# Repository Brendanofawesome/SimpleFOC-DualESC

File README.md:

# SimpleFOC Dual ESC

This repository contains the hardware design files for a compact dual-motor BLDC controller built around the SimpleFOC ecosystem.  

The board is designed to run two 3-phase motors independently with field-oriented control (FOC) using an STM32G4 microcontroller.  

It is also designed to fit under JLCPCB's $2 PCB deal with economic assembly

## What the device does

The controller takes a single high-voltage DC input and drives two BLDC motors through two independent 3-phase power stages.  
Each motor stage uses a dedicated gate driver and current-sense path so firmware can regulate torque/current, speed, and position.

At a high level, the board:

- Uses up to 36 V to power 3-phase outputs for **Motor 1** and **Motor 2**
- Uses dual DRV8323-based driver stages for 6-PWM control of each motor
- Measures phase/motor current for closed-loop control and protection
- Interfaces with Hall sensors for rotor position feedback
- Exposes control/debug interfaces including I2C, SPI headers, USB-C, reset, and programming pins

## Hardware highlights

- **MCU:** STM32G474CBTx (FOC-capable Cortex-M4)
- **Power input:** XT60 connector
- **Motor outputs:** Two MR60 3-phase motor connectors
- **Board outline:** 50 mm × 50 mm (from KiCad PCB edge cuts)
- **Power stage:** Dual 3-phase inverter architecture (6 MOSFETs per motor stage)

## Repository layout

- `specifications.md`  
  Project specification draft (electrical, control, thermal, and interface targets).
- `KiCad/simpleFOC Dual Motor Controller.kicad_pro`  
  Top-level KiCad project.
- `KiCad/simpleFOC Dual Motor Controller.kicad_sch`  
  Top-level schematic with MCU, power, interfaces, and two motor-driver hierarchical sheets.
- `KiCad/DriverStage.kicad_sch`  
  Per-motor driver stage (reused for Motor Driver 1 and Motor Driver 2).
- `KiCad/simpleFOC Dual Motor Controller.kicad_pcb`  
  PCB layout and silkscreen connector labels.

## Current status

This repo currently provides hardware design and specification files.  
Firmware implementation and full bring-up documentation are not yet included here.

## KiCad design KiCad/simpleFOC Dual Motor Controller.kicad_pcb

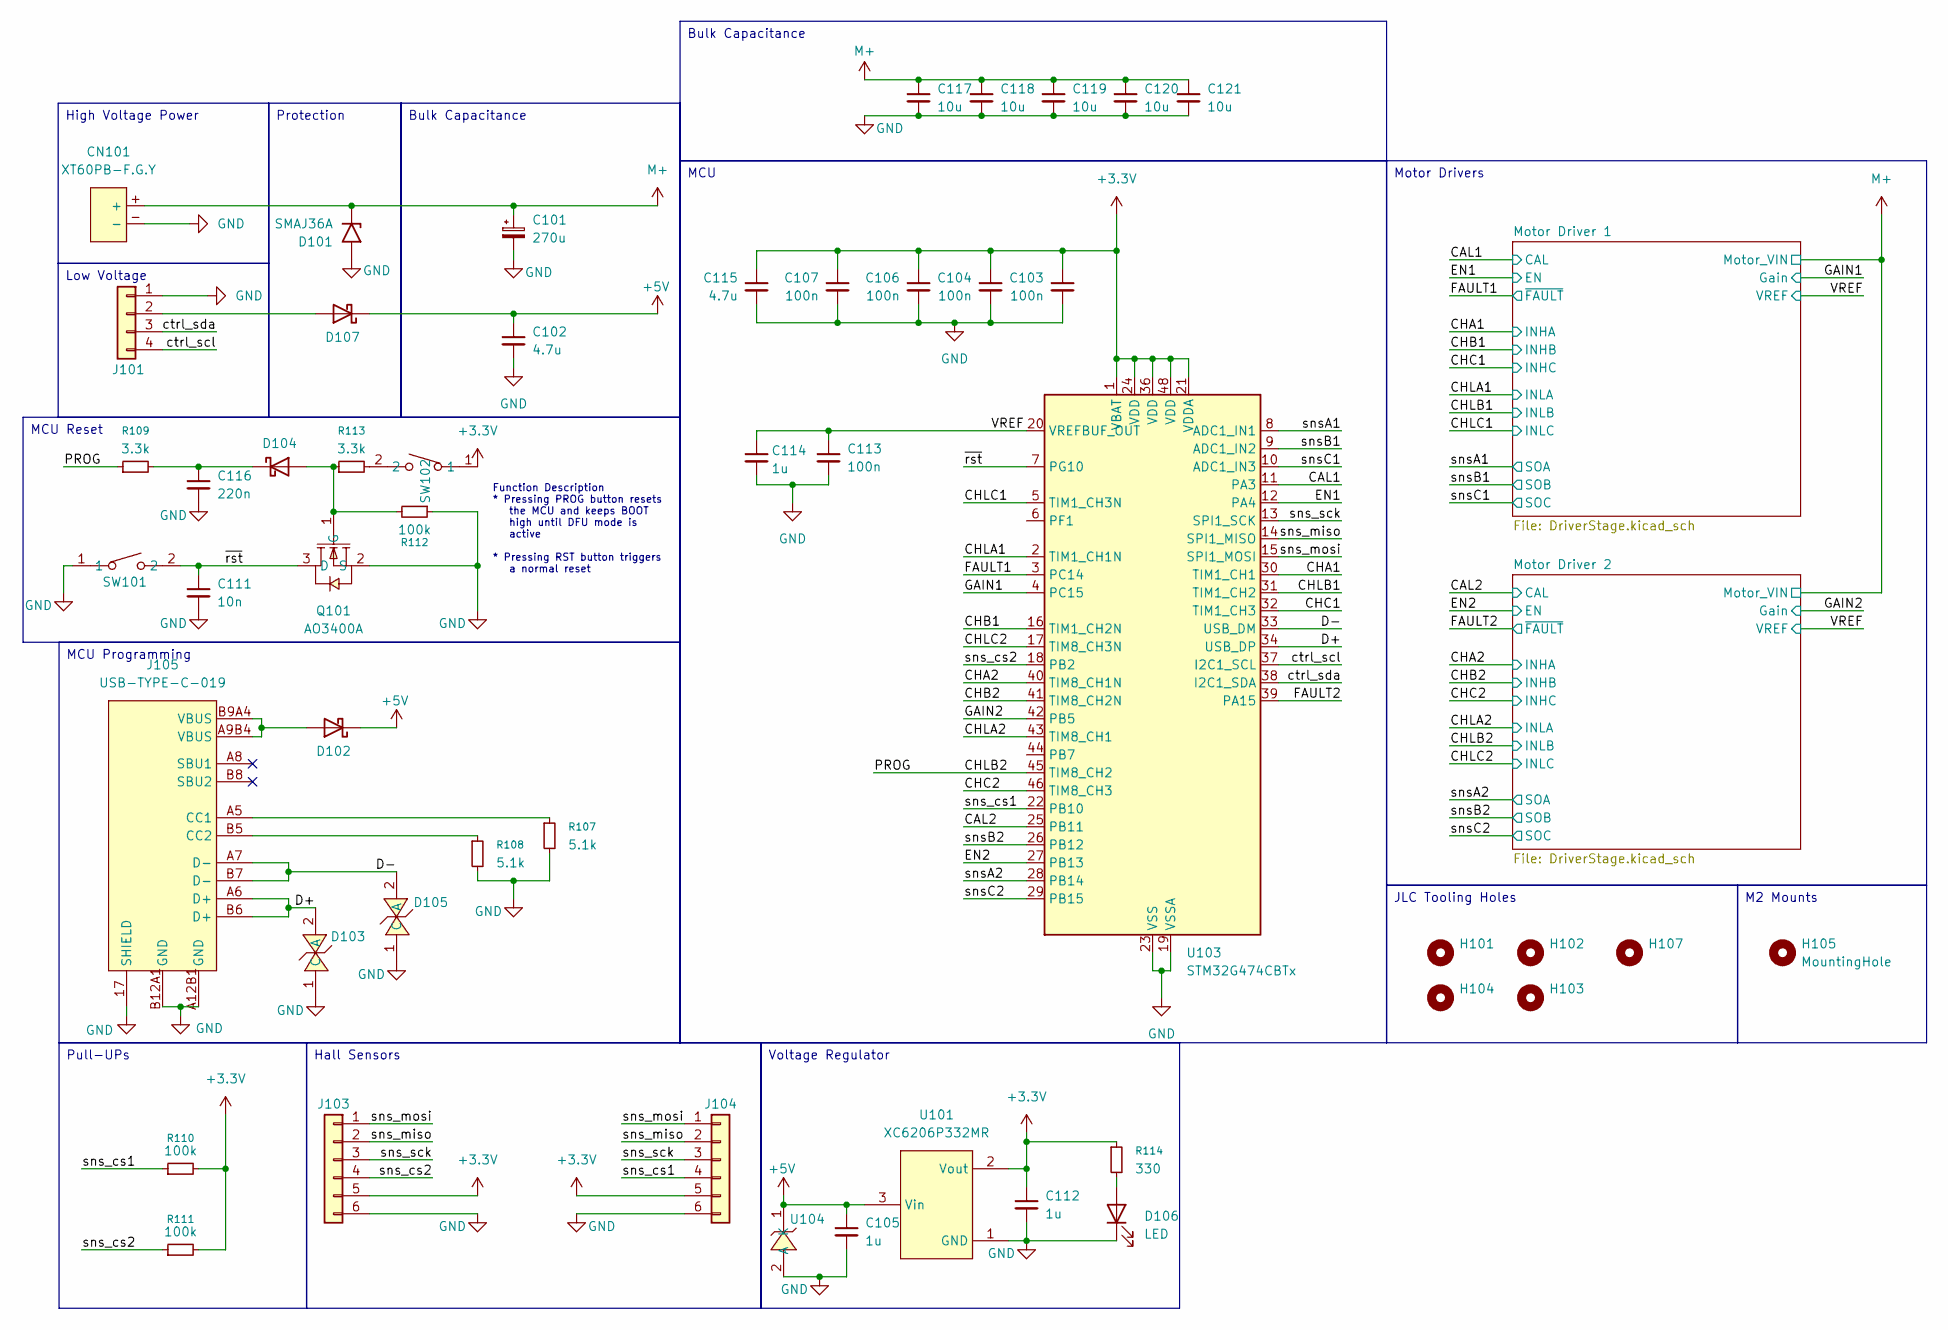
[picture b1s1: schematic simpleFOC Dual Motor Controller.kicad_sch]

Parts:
C101: 270u; CAP-TH_BD8.0-P3.50-D0.6-FD; LCSC C55079818
C102, C115: 4.7u; C_0402_1005Metric; LCSC C23733
C103, C104, C106, C107, C113: 100n; C_0402_1005Metric; LCSC C307331
C105, C112, C114: 1u; C_0402_1005Metric; LCSC C52923
C111: 10n; C_0402_1005Metric; LCSC C15195
C116: 220n; C_0402_1005Metric; LCSC C16772
C117, C118, C119, C120, C121: 10u; C_1206_3216Metric; LCSC C13585
CN101: XT60PB-F.G.Y; CONN-TH_XT60PB-F.G.Y; MPN XT60PB-F.G.Y; LCSC Part C19268038
D101: SMAJ36A; D_SMA; LCSC C19077550
D102, D104, D107: 1N5819WS; D_SOD-323; LCSC C191023
D103, D105: H5VL10B; SOD-882_L1.0-W0.6-BI; MPN H5VL10B; LCSC Part C7420372
D106: LED; LED_0603_1608Metric; LCSC C2290
H101, H102, H103, H104, H107: MountingHole; JLC_Tooling_Hole
H105: MountingHole; MountingHole_2.2mm_M2
J101: Conn_01x04; JST_PH_B4B-PH-K_1x04_P2.00mm_Vertical; LCSC C131334
J103, J104: Conn_01x06; JST_PH_B6B-PH-K_1x06_P2.00mm_Vertical; LCSC C131342
J105: USB-TYPE-C-019; TYPE-C-SMD_HX-TYPE-C-16PIN; MPN USB-TYPE-C-019; LCSC Part C2927039
Q101: AO3400A; SOT-23-3_L2.9-W1.3-P1.90-LS2.4-BR; MPN AO3400A; LCSC Part C20917
R107, R108: 5.1k; R_0402_1005Metric; LCSC C25905
R109, R113: 3.3k; R_0402_1005Metric; LCSC C25890
R110, R111, R112: 100k; R_0402_1005Metric; LCSC C25741
R114: 330; R_0402_1005Metric; LCSC C25104
SW101, SW102: TS-1088-AR02016; SW-SMD_L3.9-W3.0-P4.45; MPN TS-1088-AR02016; LCSC Part C720477
U101: XC6206P332MR; SOT-23-3_L2.9-W1.6-P1.90-LS2.8-BR; MPN XC6206P332MR-G; LCSC Part C5446
U103: STM32G474CBTx; LQFP-48_7x7mm_P0.5mm; LCSC C730123
U104: H5VND5UB; SOD-523F_L1.7-W0.9-LS1.7-RD; MPN H5VND5UB; LCSC Part C20615819

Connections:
+3.3V: C103.1, C104.1, C106.1, C107.1, C112.1, C115.1, J103.5, J104.5, R110.2, R111.2, R114.1, SW102.1, U101.2 (Vout), U103.1 (VBAT), U103.21 (VDDA), U103.24 (VDD), U103.36 (VDD), U103.48 (VDD); also elsewhere on the board
+5V: C102.1, C105.1, D102.1 (K), D107.1 (K), U101.3 (Vin), U104.1 (K)
/CAL1: U103.11 (PA3); also elsewhere on the board
/CAL2: U103.25 (PB11); also elsewhere on the board
/CHA1: U103.30 (TIM1_CH1); also elsewhere on the board
/CHA2: U103.40 (TIM8_CH1N); also elsewhere on the board
/CHB1: U103.16 (TIM1_CH2N); also elsewhere on the board
/CHB2: U103.41 (TIM8_CH2N); also elsewhere on the board
/CHC1: U103.32 (TIM1_CH3); also elsewhere on the board
/CHC2: U103.46 (TIM8_CH3); also elsewhere on the board
/CHLA1: U103.2 (TIM1_CH1N); also elsewhere on the board
/CHLA2: U103.43 (TIM8_CH1); also elsewhere on the board
/CHLB1: U103.31 (TIM1_CH2); also elsewhere on the board
/CHLB2: R109.1, U103.45 (TIM8_CH2); also elsewhere on the board
/CHLC1: U103.5 (TIM1_CH3N); also elsewhere on the board
/CHLC2: U103.17 (TIM8_CH3N); also elsewhere on the board
/D+: D103.2 (A), J105.A6 (D+), J105.B6 (D+), U103.34 (USB_DP)
/D-: D105.2 (A), J105.A7 (D-), J105.B7 (D-), U103.33 (USB_DM)
/EN1: U103.12 (PA4); also elsewhere on the board
/EN2: U103.27 (PB13); also elsewhere on the board
/FAULT1: U103.3 (PC14); also elsewhere on the board
/FAULT2: U103.39 (PA15); also elsewhere on the board
/GAIN1: U103.4 (PC15); also elsewhere on the board
/GAIN2: U103.42 (PB5); also elsewhere on the board
/VREF: C113.1, C114.1, U103.20 (VREFBUF_OUT); also elsewhere on the board
/ctrl_scl: J101.4, U103.37 (I2C1_SCL)
/ctrl_sda: J101.3, U103.38 (I2C1_SDA)
/snsA1: U103.8 (ADC1_IN1); also elsewhere on the board
/snsA2: U103.28 (PB14); also elsewhere on the board
/snsB1: U103.9 (ADC1_IN2); also elsewhere on the board
/snsB2: U103.26 (PB12); also elsewhere on the board
/snsC1: U103.10 (ADC1_IN3); also elsewhere on the board
/snsC2: U103.29 (PB15); also elsewhere on the board
/sns_cs1: J104.4, R110.1, U103.22 (PB10)
/sns_cs2: J103.4, R111.1, U103.18 (PB2)
/sns_miso: J103.2, J104.2, U103.14 (SPI1_MISO)
/sns_mosi: J103.1, J104.1, U103.15 (SPI1_MOSI)
/sns_sck: J103.3, J104.3, U103.13 (SPI1_SCK)
/~rst: C111.1, Q101.3 (D), SW101.2, U103.7 (PG10)
GND: C101.2, C102.2, C103.2, C104.2, C105.2, C106.2, C107.2, C111.2, C112.2, C113.2, C114.2, C115.2, C116.2, C117.2, C118.2, C119.2, C120.2, C121.2, CN101.-, D101.2 (A2), D103.1 (C), D105.1 (C), D106.1 (K), J101.1, J103.6, J104.6, J105.17 (SHIELD), J105.A12B1 (GND), J105.B12A1 (GND), Q101.2 (S), R107.2, R108.2, R112.1, SW101.1, U101.1 (GND), U103.19 (VSSA), U103.23 (VSS), U103.35 (VSS), U103.47 (VSS), U104.2 (A); also elsewhere on the board
M+: C101.1, C117.1, C118.1, C119.1, C120.1, C121.1, CN101.+, D101.1 (A1); also elsewhere on the board
unnamed: D102.2 (A), J105.A9B4 (VBUS), J105.B9A4 (VBUS)
unnamed: D104.2 (A), Q101.1 (G), R112.2, R113.1
unnamed: C116.1, D104.1 (K), R109.2
unnamed: D106.2 (A), R114.2
unnamed: D107.2 (A), J101.2
unnamed: J105.A5 (CC1), R107.1
unnamed: J105.B5 (CC2), R108.1
unnamed: R113.2, SW102.2

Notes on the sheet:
Function Description * Pressing PROG button resets the MCU and keeps BOOT high until DFU mode is active * Pressing RST button triggers a normal reset
MCU
MCU Reset
Bulk Capacitance
Pull-UPs
JLC Tooling Holes
High Voltage Power
Hall Sensors
Protection
Motor Drivers
Low Voltage
Voltage Regulator
M2 Mounts
MCU Programming

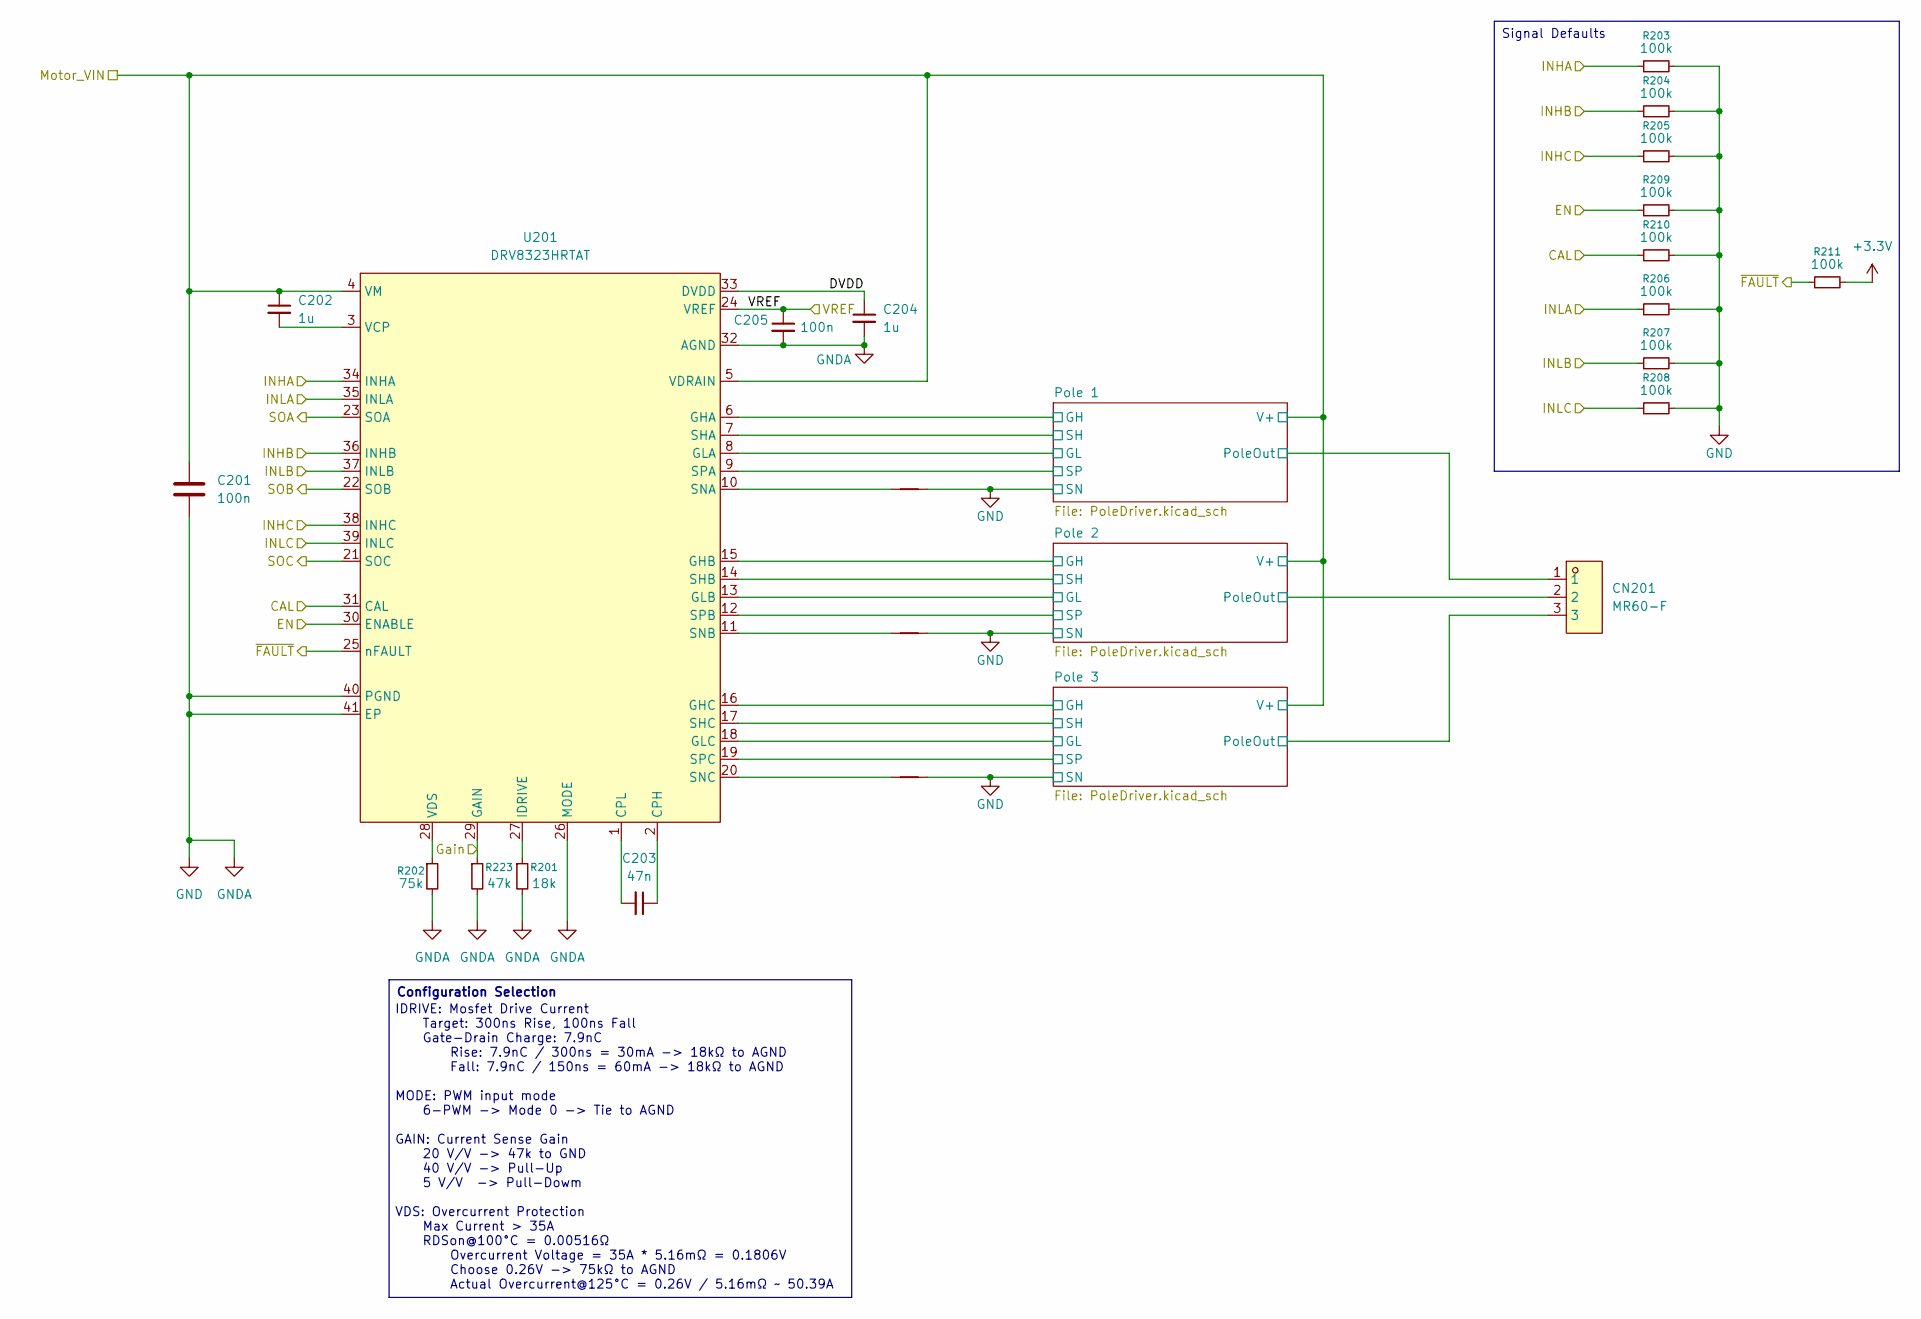
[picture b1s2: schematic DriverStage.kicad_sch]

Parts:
C201, C205: 100n; C_0402_1005Metric; LCSC C307331
C202: 1u; C_0603_1608Metric; LCSC C15849
C203: 47n; C_0603_1608Metric; LCSC C1622
C204: 1u; C_0402_1005Metric; LCSC C52923
CN201: MR60-F; CONN-TH_3P-P5.50_MR60-F; MPN MR60-F; LCSC Part C9900023305
NT201, NT202, NT203: NetTie_2; NetTie0.127mm
R201: 18k; R_0402_1005Metric; LCSC C25762
R202: 75k; R_0402_1005Metric; LCSC C25798
R203, R204, R205, R206, R207, R208, R209, R210, R211: 100k; R_0402_1005Metric; LCSC C25741
R223: 47k; R_0402_1005Metric; LCSC C25792
U201: DRV8323HRTAT; WQFN-40_L6.0-W6.0-P0.50-TL-EP4.2; MPN DRV8323HRTAT; LCSC Part C2150673

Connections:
+3.3V: R211.2; also elsewhere on the board
/CAL1: R210.1, U201.31 (CAL); also elsewhere on the board
/CHA1: R203.1, U201.34 (INHA); also elsewhere on the board
/CHB1: R204.1, U201.36 (INHB); also elsewhere on the board
/CHC1: R205.1, U201.38 (INHC); also elsewhere on the board
/CHLA1: R206.1, U201.35 (INLA); also elsewhere on the board
/CHLB1: R207.1, U201.37 (INLB); also elsewhere on the board
/CHLC1: R208.1, U201.39 (INLC); also elsewhere on the board
/EN1: R209.1, U201.30 (ENABLE); also elsewhere on the board
/FAULT1: R211.1, U201.25 (nFAULT); also elsewhere on the board
/GAIN1: R223.1, U201.29 (GAIN); also elsewhere on the board
/Motor Driver 1/DVDD: C204.1, U201.33 (DVDD)
/Motor Driver 1/Pole 1/GH: U201.6 (GHA); also elsewhere on the board
/Motor Driver 1/Pole 1/GL: U201.8 (GLA); also elsewhere on the board
/Motor Driver 1/Pole 1/PoleOut: CN201.1, U201.7 (SHA); also elsewhere on the board
/Motor Driver 1/Pole 1/SP: U201.9 (SPA); also elsewhere on the board
/Motor Driver 1/Pole 2/GH: U201.15 (GHB); also elsewhere on the board
/Motor Driver 1/Pole 2/GL: U201.13 (GLB); also elsewhere on the board
/Motor Driver 1/Pole 2/PoleOut: CN201.2, U201.14 (SHB); also elsewhere on the board
/Motor Driver 1/Pole 2/SP: U201.12 (SPB); also elsewhere on the board
/Motor Driver 1/Pole 3/GH: U201.16 (GHC); also elsewhere on the board
/Motor Driver 1/Pole 3/GL: U201.18 (GLC); also elsewhere on the board
/Motor Driver 1/Pole 3/PoleOut: CN201.3, U201.17 (SHC); also elsewhere on the board
/Motor Driver 1/Pole 3/SP: U201.19 (SPC); also elsewhere on the board
/VREF: C205.1, U201.24 (VREF); also elsewhere on the board
/snsA1: U201.23 (SOA); also elsewhere on the board
/snsB1: U201.22 (SOB); also elsewhere on the board
/snsC1: U201.21 (SOC); also elsewhere on the board
GND: C201.2, C204.2, C205.2, NT201.2, NT202.2, NT203.2, R201.2, R202.2, R203.2, R204.2, R205.2, R206.2, R207.2, R208.2, R209.2, R210.2, R223.2, U201.26 (MODE), U201.32 (AGND), U201.40 (PGND), U201.41 (EP); also elsewhere on the board
M+: C201.1, C202.1, U201.4 (VM), U201.5 (VDRAIN); also elsewhere on the board
unnamed: C203.1, U201.2 (CPH)
unnamed: C203.2, U201.1 (CPL)
unnamed: R201.1, U201.27 (IDRIVE)
unnamed: NT201.1, U201.10 (SNA)
unnamed: NT202.1, U201.11 (SNB)
unnamed: NT203.1, U201.20 (SNC)
unnamed: C202.2, U201.3 (VCP)
unnamed: R202.1, U201.28 (VDS)

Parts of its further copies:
C206, C209: 100n; C_0402_1005Metric; LCSC C307331
C207: 1u; C_0603_1608Metric; LCSC C15849
C208: 47n; C_0603_1608Metric; LCSC C1622
C210: 1u; C_0402_1005Metric; LCSC C52923
CN202: MR60-F; CONN-TH_3P-P5.50_MR60-F; MPN MR60-F; LCSC Part C9900023305
NT204, NT205, NT206: NetTie_2; NetTie0.127mm
R212: 75k; R_0402_1005Metric; LCSC C25798
R213: 18k; R_0402_1005Metric; LCSC C25762
R214, R215, R216, R220, R221, R222, R602, R603, R604: 100k; R_0402_1005Metric; LCSC C25741
R601: 47k; R_0402_1005Metric; LCSC C25792
U202: DRV8323HRTAT; WQFN-40_L6.0-W6.0-P0.50-TL-EP4.2; MPN DRV8323HRTAT; LCSC Part C2150673

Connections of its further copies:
+3.3V: R222.2; also elsewhere on the board
/CAL2: R221.1, U202.31 (CAL); also elsewhere on the board
/CHA2: R214.1, U202.34 (INHA); also elsewhere on the board
/CHB2: R215.1, U202.36 (INHB); also elsewhere on the board
/CHC2: R216.1, U202.38 (INHC); also elsewhere on the board
/CHLA2: R602.1, U202.35 (INLA); also elsewhere on the board
/CHLB2: R603.1, U202.37 (INLB); also elsewhere on the board
/CHLC2: R604.1, U202.39 (INLC); also elsewhere on the board
/EN2: R220.1, U202.30 (ENABLE); also elsewhere on the board
/FAULT2: R222.1, U202.25 (nFAULT); also elsewhere on the board
/GAIN2: R601.1, U202.29 (GAIN); also elsewhere on the board
/Motor Driver 2/DVDD: C210.1, U202.33 (DVDD)
/Motor Driver 2/Pole 1/GH: U202.6 (GHA); also elsewhere on the board
/Motor Driver 2/Pole 1/GL: U202.8 (GLA); also elsewhere on the board
/Motor Driver 2/Pole 1/PoleOut: CN202.1, U202.7 (SHA); also elsewhere on the board
/Motor Driver 2/Pole 1/SP: U202.9 (SPA); also elsewhere on the board
/Motor Driver 2/Pole 2/GH: U202.15 (GHB); also elsewhere on the board
/Motor Driver 2/Pole 2/GL: U202.13 (GLB); also elsewhere on the board
/Motor Driver 2/Pole 2/PoleOut: CN202.2, U202.14 (SHB); also elsewhere on the board
/Motor Driver 2/Pole 2/SP: U202.12 (SPB); also elsewhere on the board
/Motor Driver 2/Pole 3/GH: U202.16 (GHC); also elsewhere on the board
/Motor Driver 2/Pole 3/GL: U202.18 (GLC); also elsewhere on the board
/Motor Driver 2/Pole 3/PoleOut: CN202.3, U202.17 (SHC); also elsewhere on the board
/Motor Driver 2/Pole 3/SP: U202.19 (SPC); also elsewhere on the board
/VREF: C209.1, U202.24 (VREF); also elsewhere on the board
/snsA2: U202.23 (SOA); also elsewhere on the board
/snsB2: U202.22 (SOB); also elsewhere on the board
/snsC2: U202.21 (SOC); also elsewhere on the board
GND: C206.2, C209.2, C210.2, NT204.2, NT205.2, NT206.2, R212.2, R213.2, R214.2, R215.2, R216.2, R220.2, R221.2, R601.2, R602.2, R603.2, R604.2, U202.26 (MODE), U202.32 (AGND), U202.40 (PGND), U202.41 (EP); also elsewhere on the board
M+: C206.1, C207.1, U202.4 (VM), U202.5 (VDRAIN); also elsewhere on the board
unnamed: C208.1, U202.2 (CPH)
unnamed: C208.2, U202.1 (CPL)
unnamed: R213.1, U202.27 (IDRIVE)
unnamed: NT204.1, U202.10 (SNA)
unnamed: NT205.1, U202.11 (SNB)
unnamed: NT206.1, U202.20 (SNC)
unnamed: C207.2, U202.3 (VCP)
unnamed: R212.1, U202.28 (VDS)

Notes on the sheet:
IDRIVE: Mosfet Drive Current Target: 300ns Rise, 100ns Fall Gate-Drain Charge: 7.9nC Rise: 7.9nC / 300ns = 30mA -> 18kΩ to AGND Fall: 7.9nC / 150ns = 60mA -> 18kΩ to AGND MODE: PWM input mode 6-PWM -> Mode 0 -> Tie to AGND GAIN: Current Sense Gain 20 V/V -> 47k to GND 40 V/V -> Pull-Up 5 V/V -> Pul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
Signal Defaults
Configuration Selection

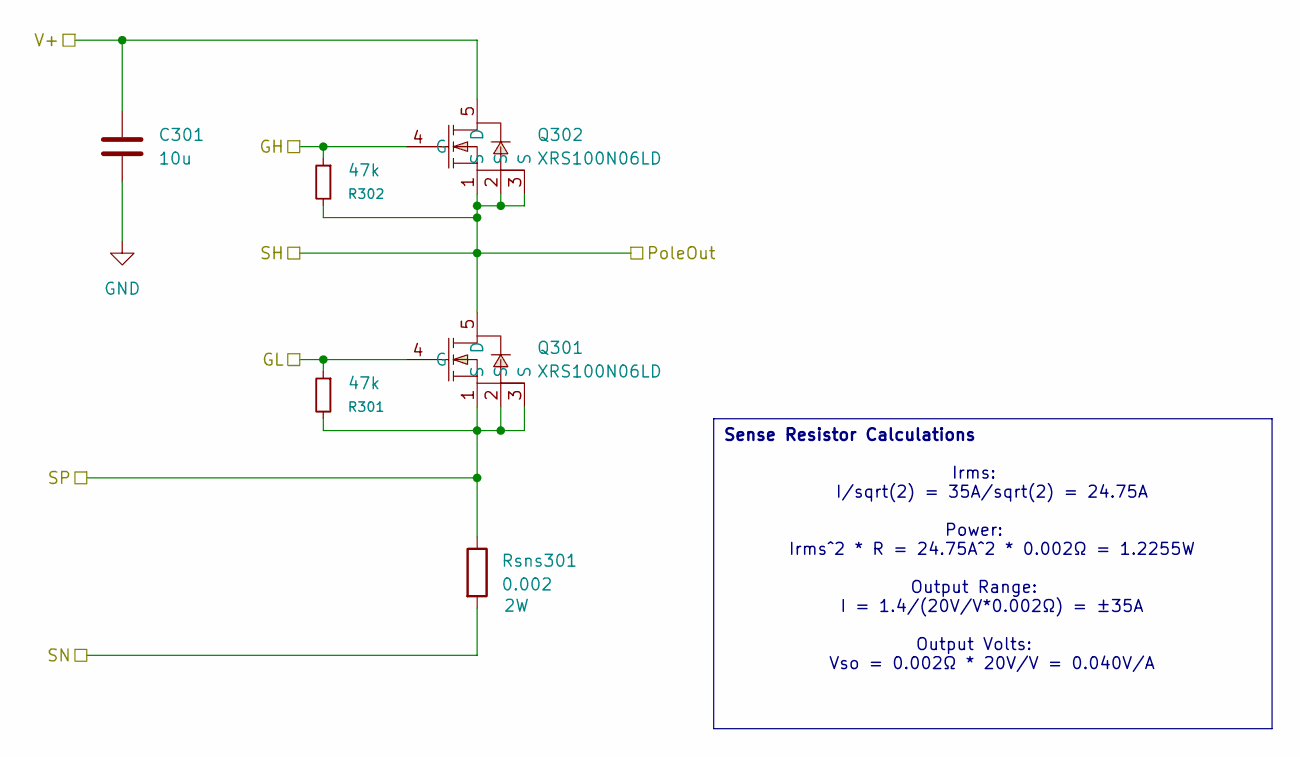
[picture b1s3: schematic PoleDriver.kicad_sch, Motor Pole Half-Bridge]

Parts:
C301: 10u; C_1206_3216Metric; LCSC C13585
Q301, Q302: XRS100N06LD; DFN-8_L3.0-W3.0-P0.65-BL-4; MPN XRS100N06LD; LCSC Part C42457038
R301, R302: 47k; R_0402_1005Metric; LCSC C25792
Rsns301: 0.002; R_2512_6332Metric; LCSC C7467245

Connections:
/Motor Driver 1/Pole 1/GH: Q302.4 (G), R302.1; also elsewhere on the board
/Motor Driver 1/Pole 1/GL: Q301.4 (G), R301.1; also elsewhere on the board
/Motor Driver 1/Pole 1/PoleOut: Q301.5 (D), Q302.1 (S), Q302.2 (S), Q302.3 (S), R302.2; also elsewhere on the board
/Motor Driver 1/Pole 1/SP: Q301.1 (S), Q301.2 (S), Q301.3 (S), R301.2, Rsns301.1; also elsewhere on the board
GND: C301.2, Rsns301.2; also elsewhere on the board
M+: C301.1, Q302.5 (D); also elsewhere on the board

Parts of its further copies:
C108, C109, C110, C401, C501: 10u; C_1206_3216Metric; LCSC C13585
Q401, Q402, Q501, Q502, Q701, Q702, Q801, Q802, Q901, Q902: XRS100N06LD; DFN-8_L3.0-W3.0-P0.65-BL-4; MPN XRS100N06LD; LCSC Part C42457038
R101, R102, R103, R104, R105, R106, R401, R402, R501, R502: 47k; R_0402_1005Metric; LCSC C25792
Rsns101, Rsns102, Rsns103, Rsns401, Rsns501: 0.002; R_2512_6332Metric; LCSC C7467245

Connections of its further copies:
/Motor Driver 1/Pole 2/GH: Q402.4 (G), R402.1; also elsewhere on the board
/Motor Driver 1/Pole 2/GL: Q401.4 (G), R401.1; also elsewhere on the board
/Motor Driver 1/Pole 2/PoleOut: Q401.5 (D), Q402.1 (S), Q402.2 (S), Q402.3 (S), R402.2; also elsewhere on the board
/Motor Driver 1/Pole 2/SP: Q401.1 (S), Q401.2 (S), Q401.3 (S), R401.2, Rsns401.1; also elsewhere on the board
/Motor Driver 1/Pole 3/GH: Q502.4 (G), R502.1; also elsewhere on the board
/Motor Driver 1/Pole 3/GL: Q501.4 (G), R501.1; also elsewhere on the board
/Motor Driver 1/Pole 3/PoleOut: Q501.5 (D), Q502.1 (S), Q502.2 (S), Q502.3 (S), R502.2; also elsewhere on the board
/Motor Driver 1/Pole 3/SP: Q501.1 (S), Q501.2 (S), Q501.3 (S), R501.2, Rsns501.1; also elsewhere on the board
/Motor Driver 2/Pole 1/GH: Q701.4 (G), R101.1; also elsewhere on the board
/Motor Driver 2/Pole 1/GL: Q702.4 (G), R104.1; also elsewhere on the board
/Motor Driver 2/Pole 1/PoleOut: Q701.1 (S), Q701.2 (S), Q701.3 (S), Q702.5 (D), R101.2; also elsewhere on the board
/Motor Driver 2/Pole 1/SP: Q702.1 (S), Q702.2 (S), Q702.3 (S), R104.2, Rsns101.1; also elsewhere on the board
/Motor Driver 2/Pole 2/GH: Q901.4 (G), R102.1; also elsewhere on the board
/Motor Driver 2/Pole 2/GL: Q902.4 (G), R105.1; also elsewhere on the board
/Motor Driver 2/Pole 2/PoleOut: Q901.1 (S), Q901.2 (S), Q901.3 (S), Q902.5 (D), R102.2; also elsewhere on the board
/Motor Driver 2/Pole 2/SP: Q902.1 (S), Q902.2 (S), Q902.3 (S), R105.2, Rsns102.1; also elsewhere on the board
/Motor Driver 2/Pole 3/GH: Q801.4 (G), R103.1; also elsewhere on the board
/Motor Driver 2/Pole 3/GL: Q802.4 (G), R106.1; also elsewhere on the board
/Motor Driver 2/Pole 3/PoleOut: Q801.1 (S), Q801.2 (S), Q801.3 (S), Q802.5 (D), R103.2; also elsewhere on the board
/Motor Driver 2/Pole 3/SP: Q802.1 (S), Q802.2 (S), Q802.3 (S), R106.2, Rsns103.1; also elsewhere on the board
GND: C108.2, C109.2, C110.2, C401.2, C501.2, Rsns101.2, Rsns102.2, Rsns103.2, Rsns401.2, Rsns501.2; also elsewhere on the board
M+: C108.1, C109.1, C110.1, C401.1, C501.1, Q402.5 (D), Q502.5 (D), Q701.5 (D), Q801.5 (D), Q901.5 (D); also elsewhere on the board

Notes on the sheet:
Irms: I/sqrt(2) = 35A/sqrt(2) = 24.75A Power: Irms^2 * R = 24.75A^2 * 0.002Ω = 1.2255W Output Range: I = 1.4/(20V/V*0.002Ω) = ±35A Output Volts: Vso = 0.002Ω * 20V/V = 0.040V/A
Sense Resistor Calculations

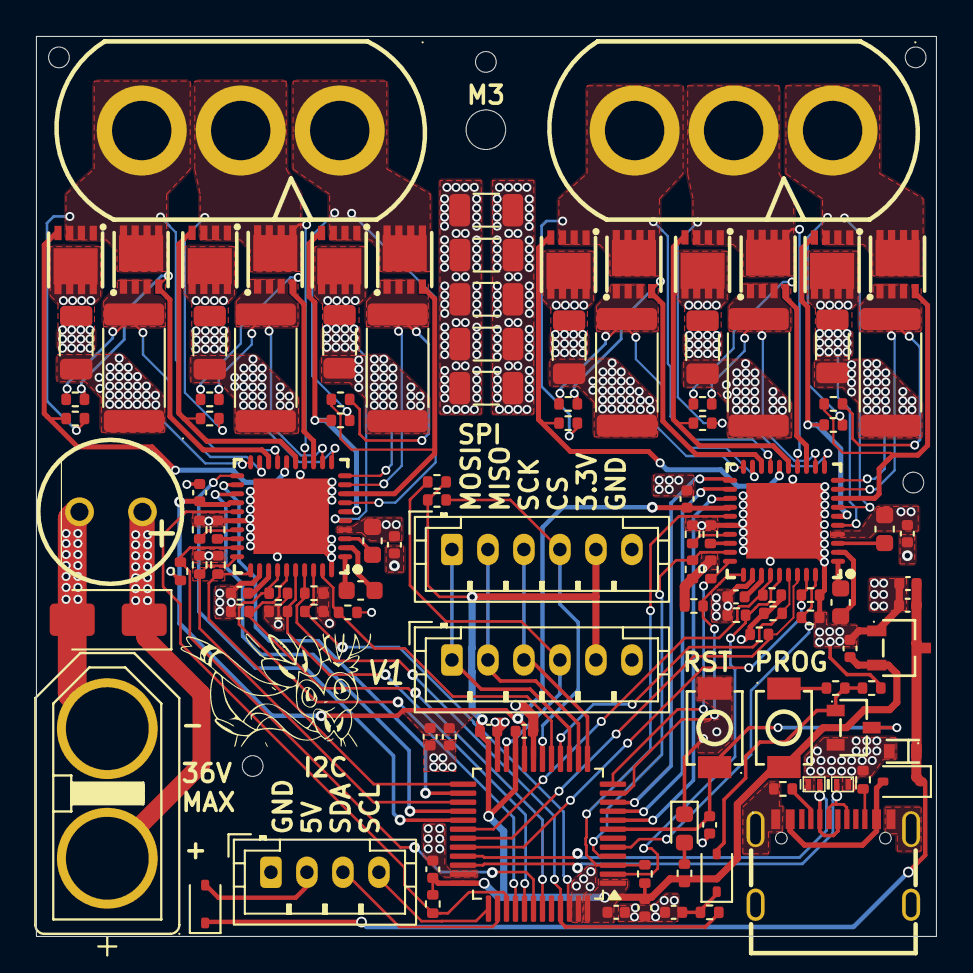
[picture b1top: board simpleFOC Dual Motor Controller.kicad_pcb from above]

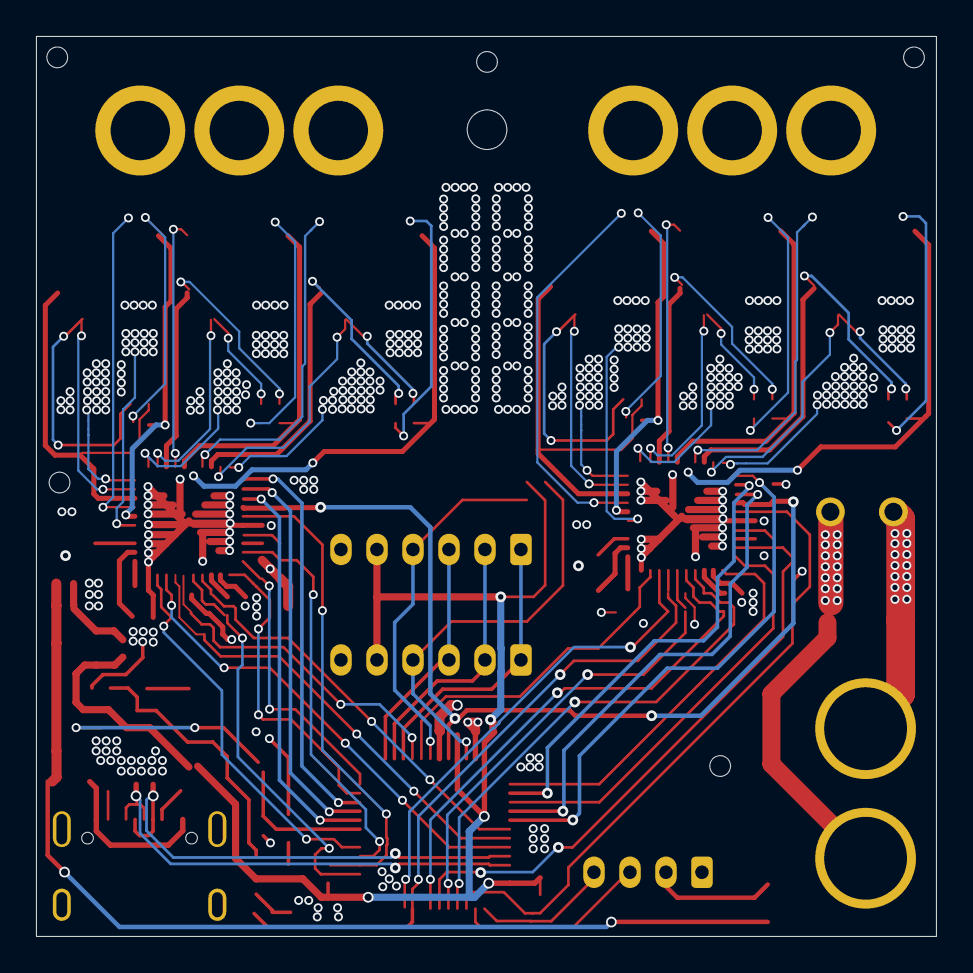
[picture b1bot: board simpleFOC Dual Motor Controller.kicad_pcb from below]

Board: 4 copper layers, 50.0 x 50.0 mm, 130 parts (6 on the bottom side), 91 nets.

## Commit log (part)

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2026-05-08 Add simpleFOC Dual Motor Controller KiCad files
    Add a complete KiCad project for the simpleFOC Dual Motor Controller: schematics (DriverStage, PoleDriver, main), PCB, project/prl/pro backup archives, symbol and footprint libraries (including easye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
2026-05-09 High current drive routing
    Add TDSON-8 3D models and footprint (.step, .wrl, .kicad_mod) and update easyeda2kicad library; modify KiCad schematic sheets (DriverStage.kicad_sch, PoleDriver.kicad_sch, simpleFOC Dual Motor Contro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
2026-05-09 added board design rules
2026-05-09 Finished wiring motor drive circuitry
2026-05-10 started adding supporting components
2026-05-11 considering using this other smaller mosfet
2026-05-11 rewired the board with smaller mosfets
2026-05-11 start adding control pins
2026-05-12 connected all control pins
2026-05-12 not sure why the schematic and pcb aren't syncing :(
2026-05-12 connected a few more signals
2026-05-13 condensed
2026-05-13 updated configuration for new mosfets
2026-05-13 swapped CPU for ESP32
2026-05-14 started laying out
2026-05-17 added hall connectors
2026-05-17 started routing
2026-05-17 mostly finished routing
2026-05-19 ESP version
2026-05-20 finished iteration 1
2026-05-20 generated production files
2026-05-21 added bulk ceramic capacitance
2026-05-23 removed old stuff from the repo
2026-06-12 created single motor PCB project
